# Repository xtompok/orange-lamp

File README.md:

# orange-lamp
PCB for PLCC4 LEDs

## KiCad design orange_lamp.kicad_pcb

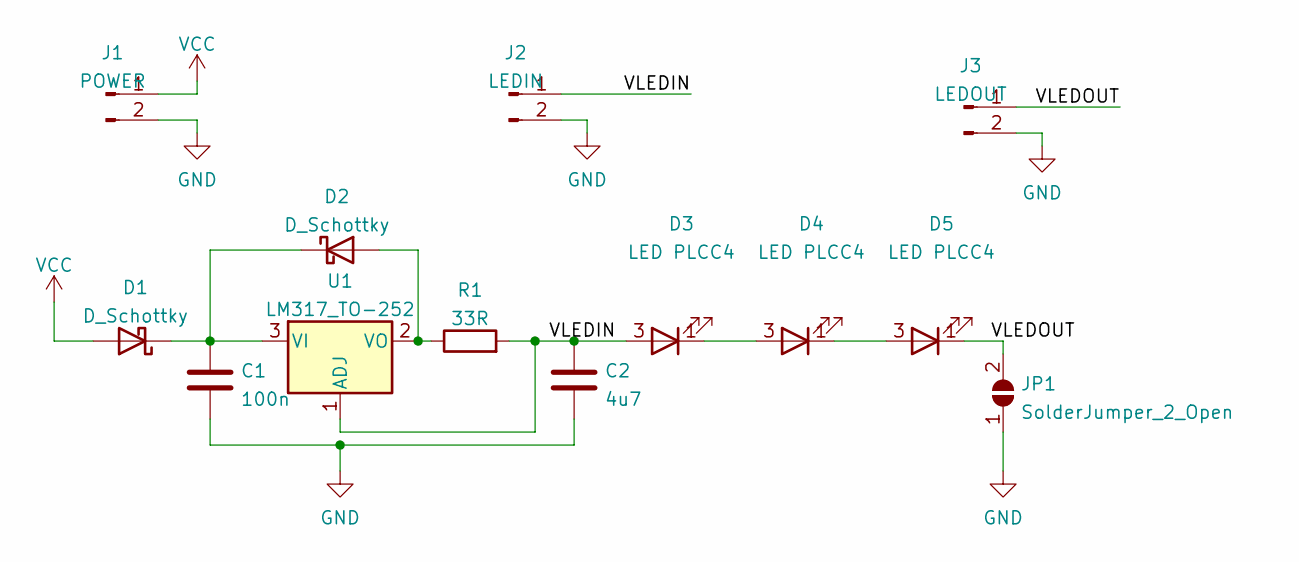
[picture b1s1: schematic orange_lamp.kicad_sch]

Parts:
C1: 100n; C_0603_1608Metric; LCSC C14663
C2: 4u7; C_1206_3216Metric; LCSC C29823
D1, D2: D_Schottky; D_SMA
D3, D4, D5: LED PLCC4; LED_Avago_PLCC4_3.2x2.8mm_CW
J1: POWER; Molex_KK-254_AE-6410-02A_1x02_P2.54mm_Vertical
J2: LEDIN; Molex_KK-254_AE-6410-02A_1x02_P2.54mm_Vertical
J3: LEDOUT; Molex_KK-254_AE-6410-02A_1x02_P2.54mm_Vertical
JP1: SolderJumper_2_Open; SolderJumper-2_P1.3mm_Open_TrianglePad1.0x1.5mm
R1: 33R; R_0805_2012Metric
U1: LM317_TO-252; TO-252-2; LCSC C75510

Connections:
/VLEDIN: C2.1, D3.3 (A), J2.1, R1.2, U1.1 (ADJ)
/VLEDOUT: D5.1 (K), J3.1, JP1.2 (B)
GND: C1.2, C2.2, J1.2, J2.2, J3.2, JP1.1 (A)
unnamed: C1.1, D1.1 (K), D2.1 (K), U1.3 (VI)
unnamed: D2.2 (A), R1.1, U1.2 (VO)
unnamed: D3.1 (K), D4.3 (A)
unnamed: D4.1 (K), D5.3 (A)
VCC: D1.2 (A), J1.1

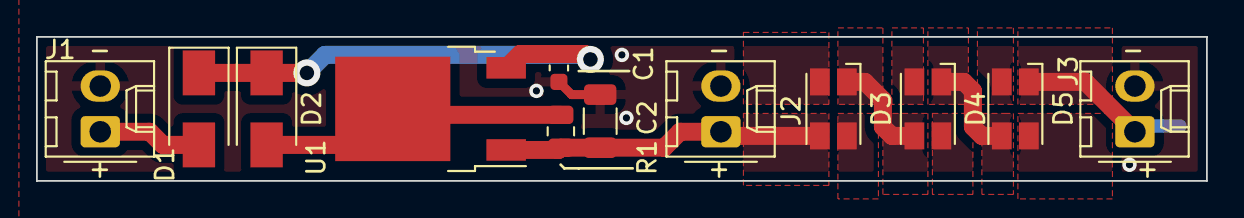
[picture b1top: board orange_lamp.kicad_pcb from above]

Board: 2 copper layers, 65.0 x 8.0 mm, 13 parts (1 on the bottom side), 8 nets.

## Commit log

2022-02-03 Added schematic and board.
2022-02-03 Final PCB.
